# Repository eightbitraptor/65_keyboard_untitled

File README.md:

# 65_keyboard_untitled

My as yet unnamed 65% keyboard design

## Project structure

- [`layouts`](layouts/) - contains all the layout options I explored and the related artifacts. Generated using [Keyboard Layout Editor](https://www.keyboard-layout-editor.com)

## Layout

**tl;dr - pretty standard 65% layout WKL bottom row and split backspace**

This keyboard is a 65% board. Which means it's basically a 60% layout that's been extended by 1 column which allows us to comfortably incorporate an arrow cluster and a couple of the useful navigation keys. It's a fixed layout because it's being built just for me as a personal project. So don't expect any allowances in plate or case design for other layouts.

It's using a HHKB style layout (ANSI base with split backspace, Esc next to the 1), a Winkeyless style bottom row with a 7u spacebar, and a 1u logo blocker in the top right (because aesthetics). The right shift has been shrunk to 1.75u to allow for the up arrow. It looks like this:

## Process

1. Decide on your layout using KLE. don't forget to either download the JSON or save your layout to Github. NOTE: To make the process easier later. I'm using the Tsangan layout to generate the platefile dxf. Tsangan is the same as WKL but with a 1u key instead of a blocker on the left side modifiers. I'm generating it this way as it makes the top case easier to design as it gives me the markings for the key that I can use as anchors in my cad program to situate the blocker.
2. copy the raw data from KLE into Swillkb. Choose cutout type and stab type - I chose simple square switch cutouts and combined cherry/co-star stab cutouts - I'm going to make the stab cutouts bigger later anyway as I want to use PCB mounted stabs.
3. Get Fusion 360 and follow along Quantriks case video, it's really good. I think I probably re-did my case 2 or three times as I understood more about Fusion in each step of the process. Also modify the design. I made the bottom/weight different as I didn't like the design in the video that much and I changed up the screw positioning and plate mounting stuff a bit. NOTE: There's no USB cutout at this point, I haven't decided where I want it yet, and there's no PCB
4. Design a PCB Schematic in KiCad. I followed along with MrKeebs videos and cross references against avrforums and some other places on the internet to verify my design. Some caveats
  - I'm using ai03's keyboard switch symbol and footprint library. I really wanted to just use the built in KiCad footprints but they don't come with a 7u spacebar, which mine is (and also has flipped stabilizers)
  - I chose the matrix layout based on the connection diagram from the kbfirmwarebuilder. I don't really know how to design a matrix other than to keep the connections as short as possible, so I went with the path of least resistance (badum tish)

## Obligatory Potato Renders

My Thinkpad struggled hard with these...

## KBFirmware Matrix map

## Resources

### Videos/reading material

- Quantrik's 65% Keyboad Case design with Fusion 360 stream
  -  https://www.youtube.com/watch?v=4P0zfLLblOw
- Mr Keebs and Gondolindri's PCB design stream series
  - https://www.youtube.com/watch?v=Nk0egpDFqRA
  - https://www.youtube.com/watch?v=beyh0__tf5M
  - https://www.youtube.com/watch?v=pllksuZwJL0

### Tools

- Keyboard Layout Editor
  - http://www.keyboard-layout-editor.com/
- Swillkb's Plate CAD builder
  - http://builder.swillkb.com/
- MrKeebs PCB Layout Creator
  - http://kbpcb.mrkeebs.com/
- Keyboard Firmware Builder
  - https://kbfirmware.com

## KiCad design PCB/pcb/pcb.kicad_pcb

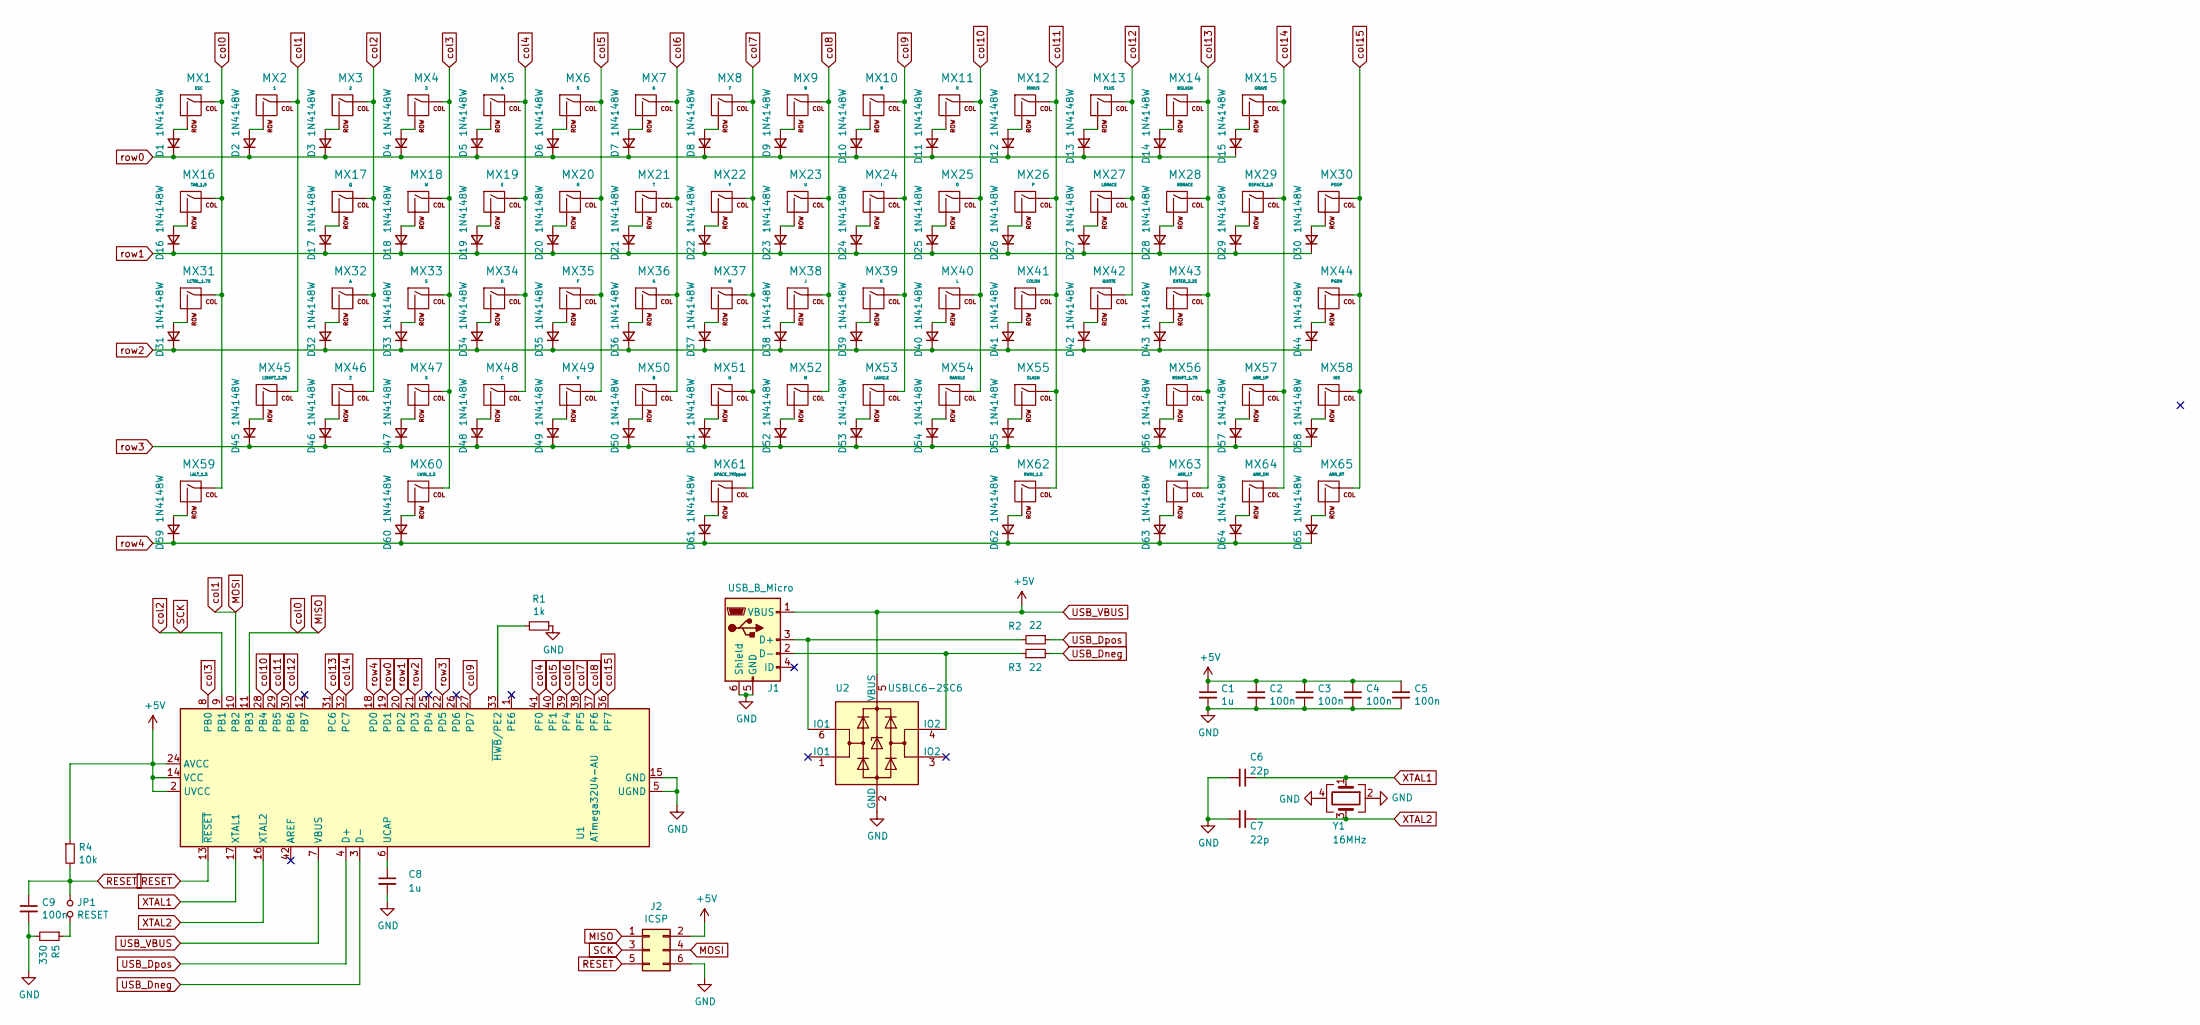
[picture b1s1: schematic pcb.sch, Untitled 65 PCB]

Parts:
C1, C8: 1u; C_0805_2012Metric_Pad1.15x1.40mm_HandSolder
C2, C3, C4, C5, C9: 100n; C_0805_2012Metric_Pad1.15x1.40mm_HandSolder
C6, C7: 22p; C_0805_2012Metric_Pad1.15x1.40mm_HandSolder
D1, D2, D3, D4, D5, D6, D7, D8, D9, D10, D11, D12, D13, D14, D15, D16, D17, D18, D19, D20, D21, D22, D23, D24, D25, D26, D27, D28, D29, D30, D31, D32, D33, D34, D35, D36, D37, D38, D39, D40, D41, D42, D43, D44, D45, D46, D47, D48, D49, D50, D51, D52, D53, D54, D55, D56, D57, D58, D59, D60, D61, D62, D63, D64, D65: 1N4148W; D_SOD-123
J1: USB_B_Micro; USB_Micro-B_GCT_USB3076-30-A
J2: ICSP; PinHeader_2x03_P2.54mm_Vertical
JP1: RESET; PinSocket_1x02_P2.54mm_Vertical
MX1: ESC; MXOnly-1U-NoLED
MX2: 1; MXOnly-1U-NoLED
MX3: 2; MXOnly-1U-NoLED
MX4: 3; MXOnly-1U-NoLED
MX5: 4; MXOnly-1U-NoLED
MX6: 5; MXOnly-1U-NoLED
MX7: 6; MXOnly-1U-NoLED
MX8: 7; MXOnly-1U-NoLED
MX9: 8; MXOnly-1U-NoLED
MX10: 9; MXOnly-1U-NoLED
MX11: 0; MXOnly-1U-NoLED
MX12: MINUS; MXOnly-1U-NoLED
MX13: PLUS; MXOnly-1U-NoLED
MX14: BSLASH; MXOnly-1U-NoLED
MX15: GRAVE; MXOnly-1U-NoLED
MX16: TAB_1.5; MXOnly-1.5U-NoLED
MX17: Q; MXOnly-1U-NoLED
MX18: W; MXOnly-1U-NoLED
MX19: E; MXOnly-1U-NoLED
MX20: R; MXOnly-1U-NoLED
MX21: T; MXOnly-1U-NoLED
MX22: Y; MXOnly-1U-NoLED
MX23: U; MXOnly-1U-NoLED
MX24: I; MXOnly-1U-NoLED
MX25: O; MXOnly-1U-NoLED
MX26: P; MXOnly-1U-NoLED
MX27: LBRACE; MXOnly-1U-NoLED
MX28: RBRACE; MXOnly-1U-NoLED
MX29: BSPACE_1.5; MXOnly-1.5U-NoLED
MX30: PGUP; MXOnly-1U-NoLED
MX31: LCTRL_1.75; MXOnly-1.75U-NoLED
MX32: A; MXOnly-1U-NoLED
MX33: S; MXOnly-1U-NoLED
MX34: D; MXOnly-1U-NoLED
MX35: F; MXOnly-1U-NoLED
MX36: G; MXOnly-1U-NoLED
MX37: H; MXOnly-1U-NoLED
MX38: J; MXOnly-1U-NoLED
MX39: K; MXOnly-1U-NoLED
MX40: L; MXOnly-1U-NoLED
MX41: COLON; MXOnly-1U-NoLED
MX42: QUOTE; MXOnly-1U-NoLED
MX43: ENTER_2.25; MXOnly-2.25U-NoLED
MX44: PGDN; MXOnly-1U-NoLED
MX45: LSHIFT_2.25; MXOnly-2.25U-NoLED
MX46: Z; MXOnly-1U-NoLED
MX47: X; MXOnly-1U-NoLED
MX48: C; MXOnly-1U-NoLED
MX49: V; MXOnly-1U-NoLED
MX50: B; MXOnly-1U-NoLED
MX51: N; MXOnly-1U-NoLED
MX52: M; MXOnly-1U-NoLED
MX53: LANGLE; MXOnly-1U-NoLED
MX54: RANGLE; MXOnly-1U-NoLED
MX55: SLASH; MXOnly-1U-NoLED
MX56: RSHIFT_1.75; MXOnly-1.75U-NoLED
MX57: ARR_UP; MXOnly-1U-NoLED
MX58: INS; MXOnly-1U-NoLED
MX59: LALT_1.5; MXOnly-1.5U-NoLED
MX60: LWIN_1.5; MXOnly-1.5U-NoLED
MX61: SPACE_7flipped; MXOnly-7U-ReversedStabilizers-NoLED
MX62: RWIN_1.5; MXOnly-1.5U-NoLED
MX63: ARR_LT; MXOnly-1U-NoLED
MX64: ARR_DN; MXOnly-1U-NoLED
MX65: ARR_RT; MXOnly-1U-NoLED
R1: 1k; R_1206_3216Metric_Pad1.42x1.75mm_HandSolder
R2, R3: 22; R_1206_3216Metric_Pad1.42x1.75mm_HandSolder
R4: 10k; R_1206_3216Metric_Pad1.42x1.75mm_HandSolder
R5: 330; R_1206_3216Metric_Pad1.42x1.75mm_HandSolder
U1: ATmega32U4-AU; TQFP-44_10x10mm_P0.8mm
U2: USBLC6-2SC6; SOT-23-6
Y1: 16MHz; Crystal_SMD_5032-4Pin_5.0x3.2mm

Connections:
GND: C1.2, C2.2, C3.2, C4.2, C5.2, C6.2, C7.2, C8.2, C9.2, J1.5 (GND), J1.6 (Shield), J2.6, R1.1, R5.2, U1.5 (UGND), U1.15 (GND), U1.23 (GND), U1.35 (GND), U1.43 (GND), U2.2 (GND), Y1.2, Y1.4
MISO: J2.1, MX1.1 (COL), MX16.1 (COL), MX31.1 (COL), MX59.1 (COL), U1.11 (PB3)
MOSI: J2.4, MX2.1 (COL), MX45.1 (COL), U1.10 (PB2)
unnamed: C8.1, U1.6 (UCAP)
unnamed: D1.2 (A), MX1.2 (ROW)
unnamed: D2.2 (A), MX2.2 (ROW)
unnamed: D3.2 (A), MX3.2 (ROW)
unnamed: D4.2 (A), MX4.2 (ROW)
unnamed: D5.2 (A), MX5.2 (ROW)
unnamed: D6.2 (A), MX6.2 (ROW)
unnamed: D7.2 (A), MX7.2 (ROW)
unnamed: D8.2 (A), MX8.2 (ROW)
unnamed: D9.2 (A), MX9.2 (ROW)
unnamed: D10.2 (A), MX10.2 (ROW)
unnamed: D11.2 (A), MX11.2 (ROW)
unnamed: D12.2 (A), MX12.2 (ROW)
unnamed: D13.2 (A), MX13.2 (ROW)
unnamed: D14.2 (A), MX14.2 (ROW)
unnamed: D15.2 (A), MX15.2 (ROW)
unnamed: D16.2 (A), MX16.2 (ROW)
unnamed: D17.2 (A), MX17.2 (ROW)
unnamed: D18.2 (A), MX18.2 (ROW)
unnamed: D19.2 (A), MX19.2 (ROW)
unnamed: D20.2 (A), MX20.2 (ROW)
unnamed: D21.2 (A), MX21.2 (ROW)
unnamed: D22.2 (A), MX22.2 (ROW)
unnamed: D23.2 (A), MX23.2 (ROW)
unnamed: D24.2 (A), MX24.2 (ROW)
unnamed: D25.2 (A), MX25.2 (ROW)
unnamed: D26.2 (A), MX26.2 (ROW)
unnamed: D27.2 (A), MX27.2 (ROW)
unnamed: D28.2 (A), MX28.2 (ROW)
unnamed: D29.2 (A), MX29.2 (ROW)
unnamed: D30.2 (A), MX30.2 (ROW)
unnamed: D31.2 (A), MX31.2 (ROW)
unnamed: D32.2 (A), MX32.2 (ROW)
unnamed: D33.2 (A), MX33.2 (ROW)
unnamed: D34.2 (A), MX34.2 (ROW)
unnamed: D35.2 (A), MX35.2 (ROW)
unnamed: D36.2 (A), MX36.2 (ROW)
unnamed: D37.2 (A), MX37.2 (ROW)
unnamed: D38.2 (A), MX38.2 (ROW)
unnamed: D39.2 (A), MX39.2 (ROW)
unnamed: D40.2 (A), MX40.2 (ROW)
unnamed: D41.2 (A), MX41.2 (ROW)
unnamed: D42.2 (A), MX42.2 (ROW)
unnamed: D43.2 (A), MX43.2 (ROW)
unnamed: D44.2 (A), MX44.2 (ROW)
unnamed: D45.2 (A), MX45.2 (ROW)
unnamed: D46.2 (A), MX46.2 (ROW)
unnamed: D47.2 (A), MX47.2 (ROW)
unnamed: D48.2 (A), MX48.2 (ROW)
unnamed: D49.2 (A), MX49.2 (ROW)
unnamed: D50.2 (A), MX50.2 (ROW)
unnamed: D51.2 (A), MX51.2 (ROW)
unnamed: D52.2 (A), MX52.2 (ROW)
unnamed: D53.2 (A), MX53.2 (ROW)
unnamed: D54.2 (A), MX54.2 (ROW)
unnamed: D55.2 (A), MX55.2 (ROW)
unnamed: D56.2 (A), MX56.2 (ROW)
unnamed: D57.2 (A), MX57.2 (ROW)
unnamed: D58.2 (A), MX58.2 (ROW)
unnamed: D59.2 (A), MX59.2 (ROW)
unnamed: D60.2 (A), MX60.2 (ROW)
unnamed: D61.2 (A), MX61.2 (ROW)
unnamed: D62.2 (A), MX62.2 (ROW)
unnamed: D63.2 (A), MX63.2 (ROW)
unnamed: D64.2 (A), MX64.2 (ROW)
unnamed: D65.2 (A), MX65.2 (ROW)
unnamed: J1.2 (D-), R3.1, U2.4 (IO2)
unnamed: J1.3 (D+), R2.2, U2.6 (IO1)
unnamed: JP1.2, R5.1
unnamed: R1.2, U1.33 (~HWB~/PE2)
RESET: C9.1, J2.5, JP1.1, R4.2, U1.13 (~RESET)
SCK: J2.3, MX3.1 (COL), MX17.1 (COL), MX32.1 (COL), MX46.1 (COL), U1.9 (PB1)
USB_Dneg: R3.2, U1.3 (D-)
USB_Dpos: R2.1, U1.4 (D+)
USB_VBUS: C1.1, C2.1, C3.1, C4.1, C5.1, J1.1 (VBUS), J2.2, R4.1, U1.2 (UVCC), U1.7 (VBUS), U1.14 (VCC), U1.24 (AVCC), U1.34 (VCC), U1.44 (AVCC), U2.5 (VBUS)
XTAL1: C6.1, U1.17 (XTAL1), Y1.1
XTAL2: C7.1, U1.16 (XTAL2), Y1.3
col3: MX4.1 (COL), MX18.1 (COL), MX33.1 (COL), MX47.1 (COL), MX60.1 (COL), U1.8 (PB0)
col4: MX5.1 (COL), MX19.1 (COL), MX34.1 (COL), MX48.1 (COL), U1.41 (PF0)
col5: MX6.1 (COL), MX20.1 (COL), MX35.1 (COL), MX49.1 (COL), U1.40 (PF1)
col6: MX7.1 (COL), MX21.1 (COL), MX36.1 (COL), MX50.1 (COL), U1.39 (PF4)
col7: MX8.1 (COL), MX22.1 (COL), MX37.1 (COL), MX51.1 (COL), MX61.1 (COL), U1.38 (PF5)
col8: MX9.1 (COL), MX23.1 (COL), MX38.1 (COL), MX52.1 (COL), U1.37 (PF6)
col9: MX10.1 (COL), MX24.1 (COL), MX39.1 (COL), MX53.1 (COL), U1.27 (PD7)
col10: MX11.1 (COL), MX25.1 (COL), MX40.1 (COL), MX54.1 (COL), U1.28 (PB4)
col11: MX12.1 (COL), MX26.1 (COL), MX41.1 (COL), MX55.1 (COL), MX62.1 (COL), U1.29 (PB5)
col12: MX13.1 (COL), MX27.1 (COL), MX42.1 (COL), U1.30 (PB6)
col13: MX14.1 (COL), MX28.1 (COL), MX43.1 (COL), MX56.1 (COL), MX63.1 (COL), U1.31 (PC6)
col14: MX15.1 (COL), MX29.1 (COL), MX57.1 (COL), MX64.1 (COL), U1.32 (PC7)
col15: MX30.1 (COL), MX44.1 (COL), MX58.1 (COL), MX65.1 (COL), U1.36 (PF7)
row0: D1.1 (K), D2.1 (K), D3.1 (K), D4.1 (K), D5.1 (K), D6.1 (K), D7.1 (K), D8.1 (K), D9.1 (K), D10.1 (K), D11.1 (K), D12.1 (K), D13.1 (K), D14.1 (K), D15.1 (K), U1.19 (PD1)
row1: D16.1 (K), D17.1 (K), D18.1 (K), D19.1 (K), D20.1 (K), D21.1 (K), D22.1 (K), D23.1 (K), D24.1 (K), D25.1 (K), D26.1 (K), D27.1 (K), D28.1 (K), D29.1 (K), D30.1 (K), U1.20 (PD2)
row2: D31.1 (K), D32.1 (K), D33.1 (K), D34.1 (K), D35.1 (K), D36.1 (K), D37.1 (K), D38.1 (K), D39.1 (K), D40.1 (K), D41.1 (K), D42.1 (K), D43.1 (K), D44.1 (K), U1.21 (PD3)
row3: D45.1 (K), D46.1 (K), D47.1 (K), D48.1 (K), D49.1 (K), D50.1 (K), D51.1 (K), D52.1 (K), D53.1 (K), D54.1 (K), D55.1 (K), D56.1 (K), D57.1 (K), D58.1 (K), U1.22 (PD5)
row4: D59.1 (K), D60.1 (K), D61.1 (K), D62.1 (K), D63.1 (K), D64.1 (K), D65.1 (K), U1.18 (PD0)

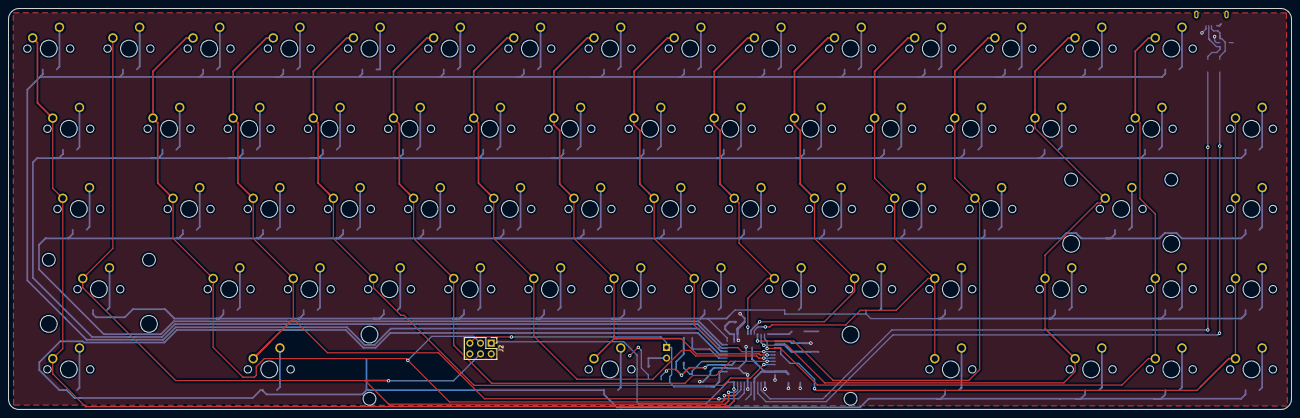
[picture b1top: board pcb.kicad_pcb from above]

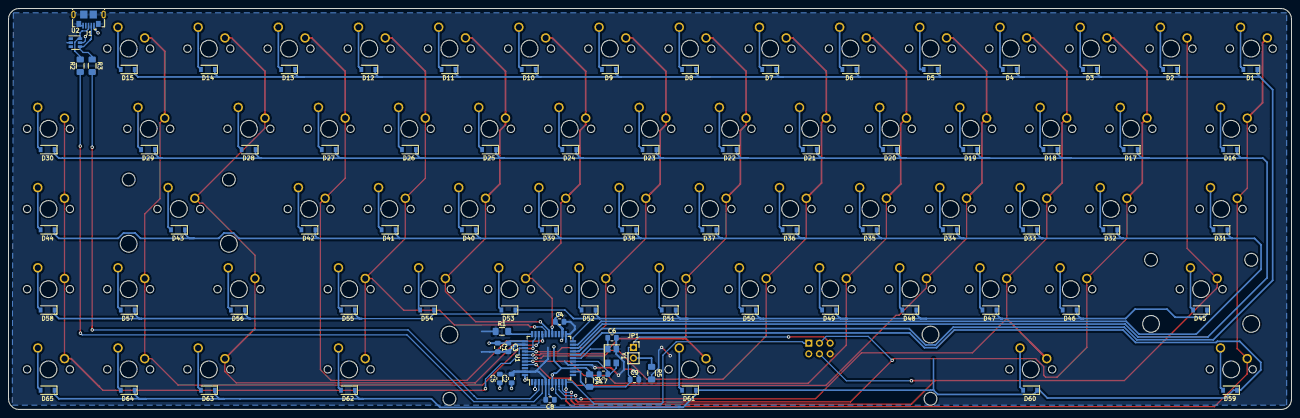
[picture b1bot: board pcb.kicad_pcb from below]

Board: 2 copper layers, 304.8 x 95.3 mm, 150 parts (84 on the bottom side), 98 nets.

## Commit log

2020-02-06 Add initial base layout options
2020-02-06 Add layout options to the readme
2020-02-07 WKL I choose you!
2020-02-07 Generate a platefile DXF and start the process of modelling it
    This used ai03's plate generator to generate a plate from the KLE raw, I
    then imported this into Fusion so I can tweak it and build the case by
    following along with Quantrik's Youtube video.
    So far I've flipped the spacebar stab and built out the case wall.
2020-02-11 Swap ai03 generated plate with swillkb
2020-02-11 Update Fusion360 files to reflect latest changes.
2020-02-12 Case Files complete except USB cut out
    I don't know where to put the USB Cutout yet as I have no PCB.
    Other than that I think we're done...
2020-02-12 Get started on the PCB layout
2020-02-12 add potato renders
2020-02-14 Refactor controller layout.
    Think that this is pretty much complete now.
    Next up the matrix
2020-02-14 Add ai03's keyboard switch lib
    KiCad has MX switches built in but nothing for a 7u spacebar :(
2020-02-14 Build the switch Matrix based on kbfirmwarebuilder
2020-02-14 reset annotations
2020-02-14 Add footprints
2020-02-17 WIP layout of PCB
2020-02-17 Layout the switches and diodes
2020-02-17 Route the matrix
2020-02-17 Clean up the project files
    * Move the submodule to where it should be in order to prevent KiCAD
    from creating a weird project file in the wrong directory
2020-02-17 Layout and generate gerbers
    The board is too big
2020-02-17 Layout the PCB and generate Gerbers.
    I am an idiot. This is my first pass at laying out the board.
    What I should have done is mark out the edge cuts and then generate a 3d
    model to import into Fusion to check that it fits in the case.
    I did not do this until after I'd layed out the board :'( and it's about
    5mm too long on each side.
    So now I need to make the board smaller by a significant amount and redo
2020-02-17 New outline (checked with Fusion model)
2020-02-18 Layout components around MC
    Move diodes to be differently oriented
2020-02-18 Finish Layout
2020-02-18 Generate Gerbers and PDF
2020-02-24 Add and ICSP connector and change some values
2020-02-27 Move the USB port and regenerate the Gerbers
2020-02-28 add latest fusion 360 backup
2020-03-02 Case progress and Renders
2020-03-02 PCB progress
2020-03-04 Add ESD Protection and make sure the fill zones are on both sides of the board
2020-03-04 Increase the distance between tracks/pads
2020-03-04 Regenerate gerbers for manufacturing
2020-03-10 Add final Gerbers and BOM generation
2020-03-11 Update Fusion 360 files
2020-05-19 add the new 3d printed design files
2020-09-02 Update STL and some GCode from the first prototype
